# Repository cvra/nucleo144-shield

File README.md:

# CVRA Nucleo144 shield

## Requirements list
* Alim en entrée
 - 5V, bus + nucleo + shield (borne à visser)
 - 6V, servo (borne à visser)
* debug connector
* 2x CAN interface with CAN transceiver:
  - 6x Connector for one CAN interface (mounted as needed)
  - 3x Connector for other CAN interface (mounted as needed)
* Interface panel connector (20 pin)
  - 5V, GND (2 pin)
  - 2x CAN for debug (1 for each interface) (4 pin)
  - RGB LED (3 GPIO to control) (3 pin)
  - I/O (11 pin)
* 15x RC-Servo output: connecteur 3pin 2.54mm standard (+,-,signal). use PWM if available and GPIO for the rest (software PWM)
* 2x Encoder connector (5-pin Molex CHA, CHB, CHN, 5V, GND)
(3x Encoder connector if I/O available on MCU)
* Additional connectors (if I/O available on MCU)
  - 1x I2C Molex
  - 1x UART Molex
  - 1x SPI Molex
  - 4x GPIO (with 4x GND) on 2.54mm standard pin holes (no connector)
  - 1x 5V power to power board and distribute over CAN
* SDCard/SPI-flash for logging
* Mechanical dimension
  - Width and length, max same as Nucleo-144 board (70mmx108mm)
  - Maximum mechanical available space including output cable for Nucleo board and shield ( height = 36mm, lenght = 136.5mm)

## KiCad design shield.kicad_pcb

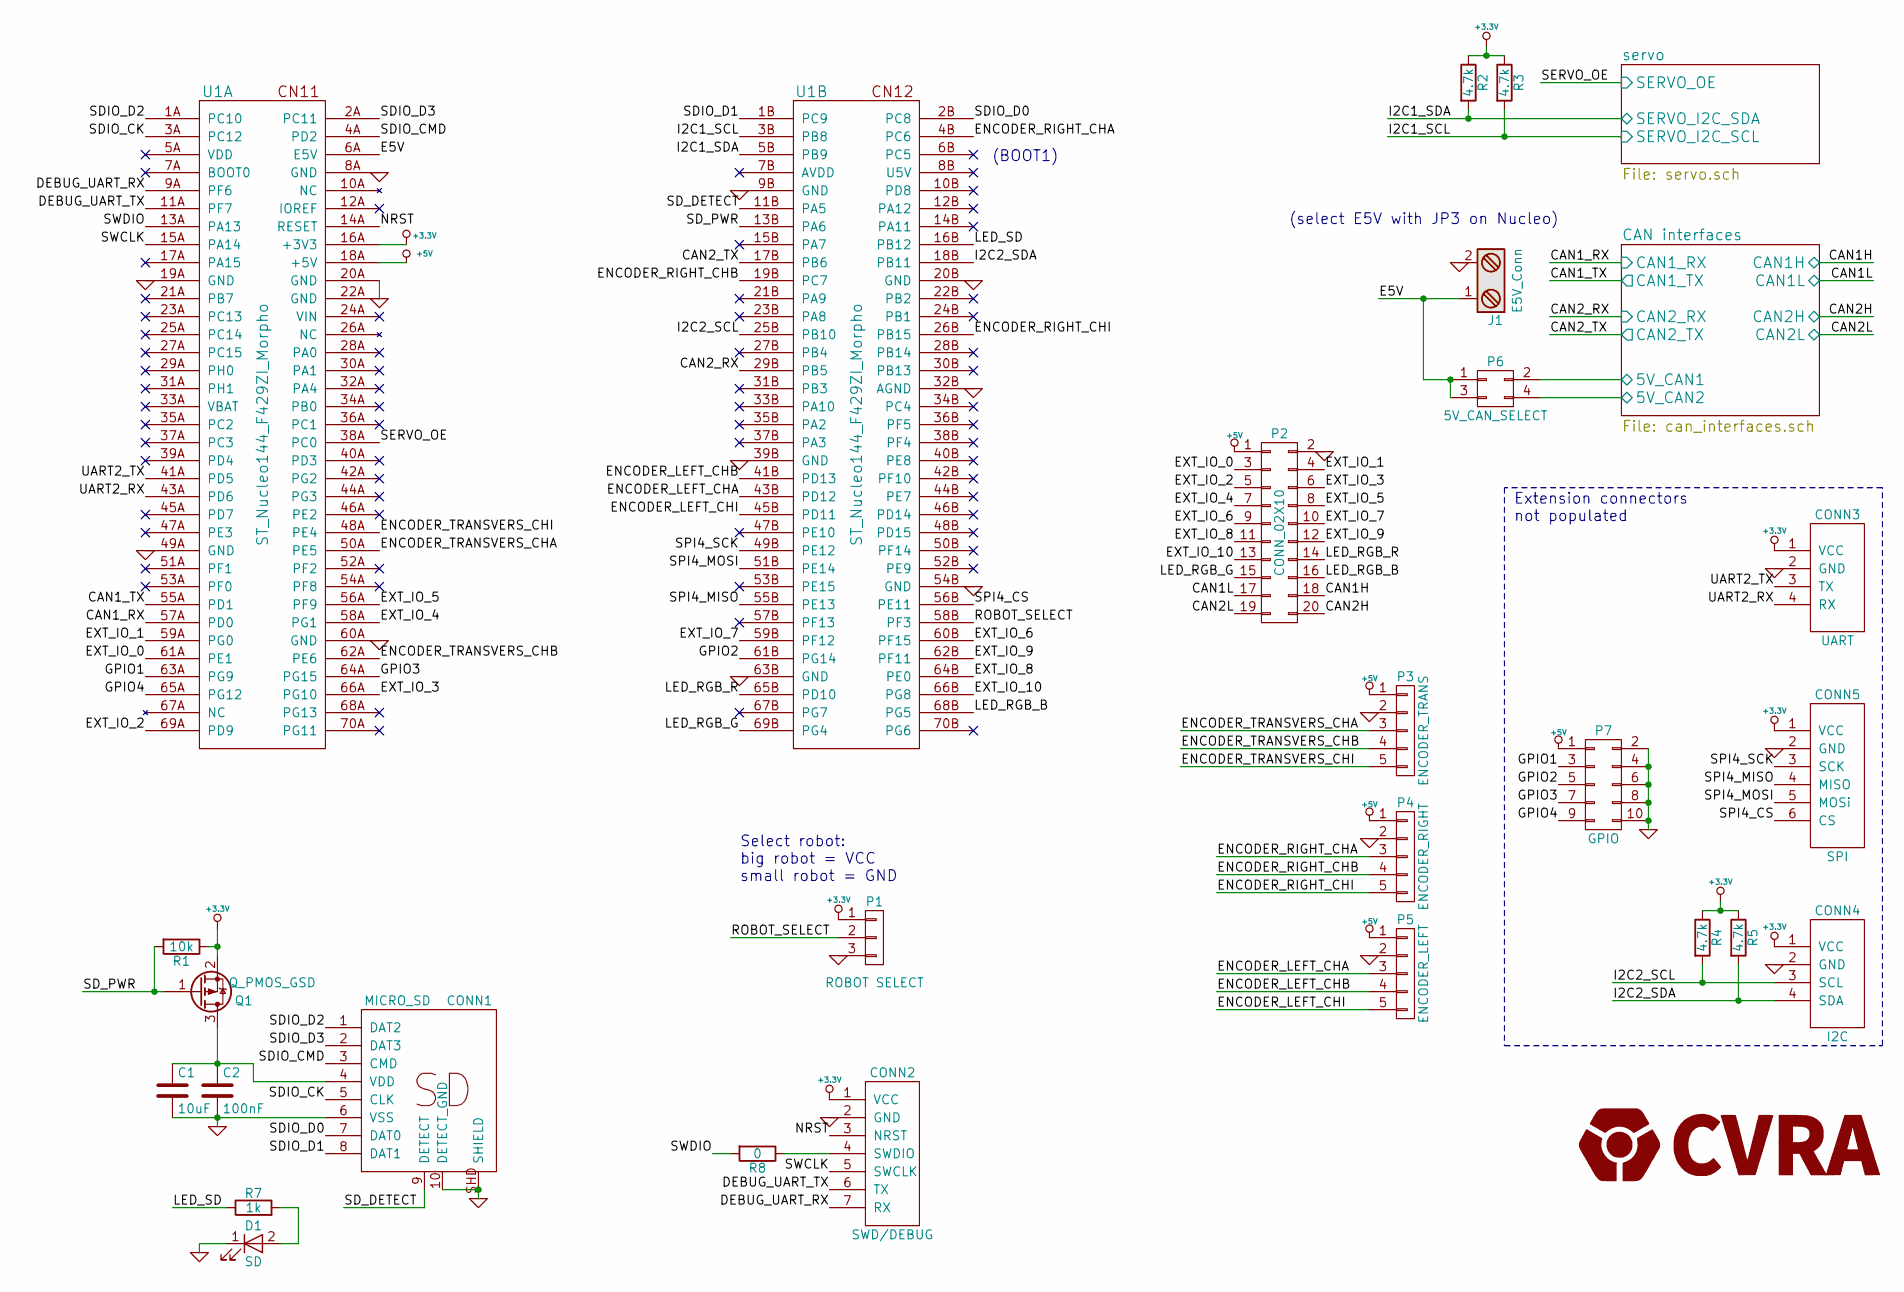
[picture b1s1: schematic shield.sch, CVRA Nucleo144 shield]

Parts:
C1: 10uF; C_0805
C2: 100nF; C_0805
CONN1: MICRO_SD; _Molex-microSD-502570-0893
CONN2: SWD/DEBUG; Molex_PicoBlade_53261-0771_07x1.25mm_Angled
CONN3: UART; Molex-PicoBlade-4
CONN4: I2C; Molex-PicoBlade-4
CONN5: SPI; Molex-PicoBlade-6
D1: SD; LED_0805
J1: E5V_Conn; TerminalBlock_Pheonix_MKDS1.5-2pol
P1: ROBOT SELECT; Pin_Header_Straight_1x03
P2: CONN_02X10; IDC_Header_Straight_20pins
P3: ENCODER_TRANS; Molex-PicoBlade-5
P4: ENCODER_RIGHT; Molex-PicoBlade-5
P5: ENCODER_LEFT; Molex-PicoBlade-5
P6: 5V_CAN_SELECT; Pin_Header_Straight_2x02
P7: GPIO; Pin_Header_Straight_2x05
Q1: Q_PMOS_GSD; SOT-23_Handsoldering
R1: 10k; R_0805
R2, R3, R4, R5: 4.7k; R_0805
R7: 1k; R_0805
R8: 0; R_0805
U1: ST_Nucleo144_F429ZI_Morpho

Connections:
+3.3V: CONN2.1 (VCC), CONN3.1 (VCC), CONN4.1 (VCC), CONN5.1 (VCC), P1.1, Q1.2 (S), R1.1, R2.1, R3.1, R4.1, R5.1, U1.16A (+3V3); also elsewhere on the board
+5V: P2.1, P3.1, P4.1, P5.1, P7.1, U1.18A (+5V); also elsewhere on the board
/CAN1H: P2.18; also elsewhere on the board
/CAN1L: P2.17; also elsewhere on the board
/CAN1_RX: U1.57A (PD0); also elsewhere on the board
/CAN1_TX: U1.55A (PD1); also elsewhere on the board
/CAN2H: P2.20; also elsewhere on the board
/CAN2L: P2.19; also elsewhere on the board
/CAN2_RX: U1.29B (PB5); also elsewhere on the board
/CAN2_TX: U1.17B (PB6); also elsewhere on the board
/CAN interfaces/5V_CAN1: P6.2; also elsewhere on the board
/CAN interfaces/5V_CAN2: P6.4; also elsewhere on the board
/DEBUG_UART_RX: CONN2.7 (RX), U1.9A (PF6)
/DEBUG_UART_TX: CONN2.6 (TX), U1.11A (PF7)
/E5V: J1.1, P6.1, P6.3, U1.6A (E5V)
/ENCODER_LEFT_CHA: P5.3, U1.43B (PD12)
/ENCODER_LEFT_CHB: P5.4, U1.41B (PD13)
/ENCODER_LEFT_CHI: P5.5, U1.45B (PD11)
/ENCODER_RIGHT_CHA: P4.3, U1.4B (PC6)
/ENCODER_RIGHT_CHB: P4.4, U1.19B (PC7)
/ENCODER_RIGHT_CHI: P4.5, U1.26B (PB15)
/ENCODER_TRANSVERS_CHA: P3.3, U1.50A (PE5)
/ENCODER_TRANSVERS_CHB: P3.4, U1.62A (PE6)
/ENCODER_TRANSVERS_CHI: P3.5, U1.48A (PE4)
/EXT_IO_0: P2.3, U1.61A (PE1)
/EXT_IO_1: P2.4, U1.59A (PG0)
/EXT_IO_2: P2.5, U1.69A (PD9)
/EXT_IO_3: P2.6, U1.66A (PG10)
/EXT_IO_4: P2.7, U1.58A (PG1)
/EXT_IO_5: P2.8, U1.56A (PF9)
/EXT_IO_6: P2.9, U1.60B (PF15)
/EXT_IO_7: P2.10, U1.59B (PF12)
/EXT_IO_8: P2.11, U1.64B (PE0)
/EXT_IO_9: P2.12, U1.62B (PF11)
/EXT_IO_10: P2.13, U1.66B (PG8)
/GPIO1: P7.3, U1.63A (PG9)
/GPIO2: P7.5, U1.61B (PG14)
/GPIO3: P7.7, U1.64A (PG15)
/GPIO4: P7.9, U1.65A (PG12)
/I2C1_SCL: R3.2, U1.3B (PB8); also elsewhere on the board
/I2C1_SDA: R2.2, U1.5B (PB9); also elsewhere on the board
/I2C2_SCL: CONN4.3 (SCL), R4.2, U1.25B (PB10)
/I2C2_SDA: CONN4.4 (SDA), R5.2, U1.18B (PB11)
/LED_RGB_B: P2.16, U1.68B (PG5)
/LED_RGB_G: P2.15, U1.69B (PG4)
/LED_RGB_R: P2.14, U1.65B (PD10)
/LED_SD: R7.1, U1.16B (PB12)
/NRST: CONN2.3 (NRST), U1.14A (RESET)
/ROBOT_SELECT: P1.2, U1.58B (PF3)
/SDIO_CK: CONN1.5 (CLK), U1.3A (PC12)
/SDIO_CMD: CONN1.3 (CMD), U1.4A (PD2)
/SDIO_D0: CONN1.7 (DAT0), U1.2B (PC8)
/SDIO_D1: CONN1.8 (DAT1), U1.1B (PC9)
/SDIO_D2: CONN1.1 (DAT2), U1.1A (PC10)
/SDIO_D3: CONN1.2 (DAT3), U1.2A (PC11)
/SD_DETECT: CONN1.9 (DETECT), U1.11B (PA5)
/SD_PWR: Q1.1 (G), R1.2, U1.13B (PA6)
/SERVO_OE: U1.38A (PC0); also elsewhere on the board
/SPI4_CS: CONN5.6 (CS), U1.56B (PE11)
/SPI4_MISO: CONN5.4 (MISO), U1.55B (PE13)
/SPI4_MOSI: CONN5.5 (MOSi), U1.51B (PE14)
/SPI4_SCK: CONN5.3 (SCK), U1.49B (PE12)
/SWCLK: CONN2.5 (SWCLK), U1.15A (PA14)
/SWDIO: R8.2, U1.13A (PA13)
/UART2_RX: CONN3.4 (RX), U1.43A (PD6)
/UART2_TX: CONN3.3 (TX), U1.41A (PD5)
GND: C1.2, C2.2, CONN1.6 (VSS), CONN1.10 (DETECT_GND), CONN1.SHD (SHIELD), CONN2.2 (GND), CONN3.2 (GND), CONN4.2 (GND), CONN5.2 (GND), D1.1 (K), J1.2, P1.3, P2.2, P3.2, P4.2, P5.2, P7.2, P7.4, P7.6, P7.8, P7.10, U1.8A (GND), U1.9B (GND), U1.19A (GND), U1.20A (GND), U1.20B (GND), U1.22A (GND), U1.32B (AGND), U1.39B (GND), U1.49A (GND), U1.54B (GND), U1.60A (GND), U1.63B (GND); also elsewhere on the board
unnamed: C1.1, C2.1, CONN1.4 (VDD), Q1.3 (D)
unnamed: CONN2.4 (SWDIO), R8.1
unnamed: D1.2 (A), R7.2

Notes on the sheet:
Select robot: big robot = VCC small robot = GND
(BOOT1)
(select E5V with JP3 on Nucleo)
Extension connectors not populated

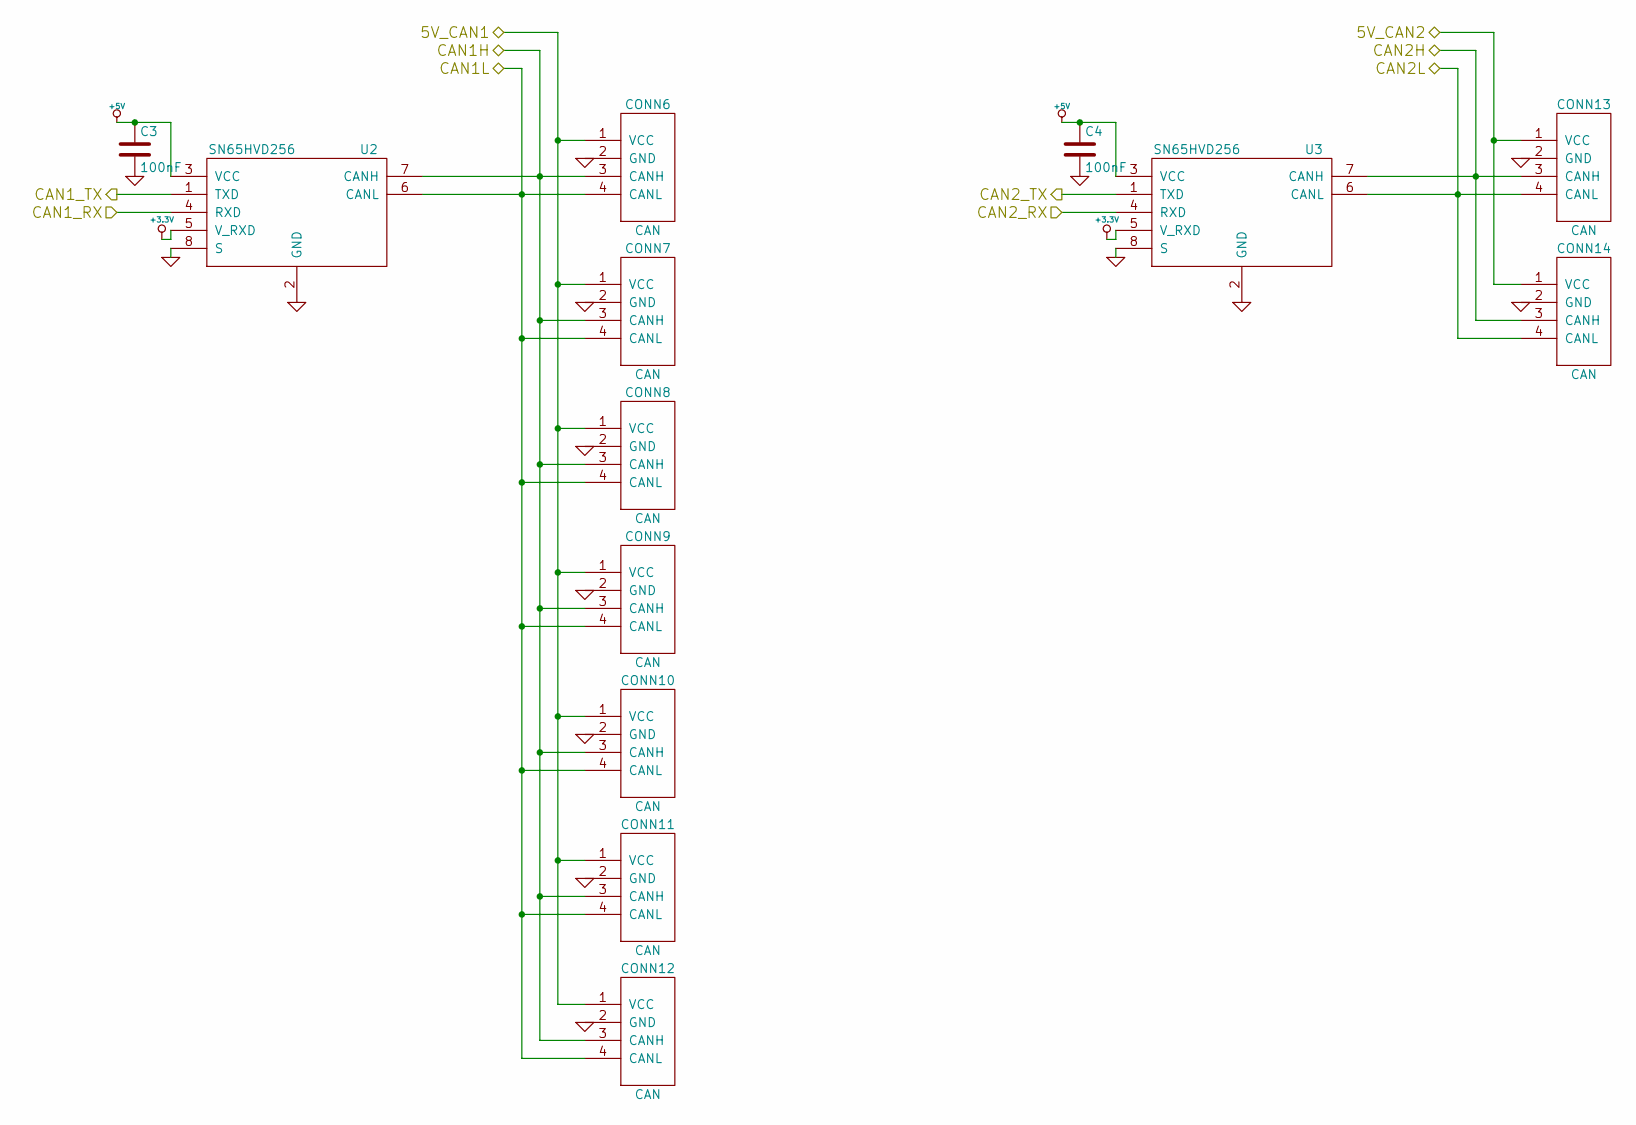
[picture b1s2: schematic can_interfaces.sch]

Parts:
C3, C4: 100nF; C_0805
CONN6, CONN7, CONN8, CONN9, CONN10, CONN11, CONN12, CONN13, CONN14: CAN; _Molex-PicoBlade-SMD-4
U2, U3: SN65HVD256; SOIC-8_3.9x4.9mm_Pitch1.27mm

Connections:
+3.3V: U2.5 (V_RXD), U3.5 (V_RXD); also elsewhere on the board
+5V: C3.1, C4.1, U2.3 (VCC), U3.3 (VCC); also elsewhere on the board
/CAN1H: CONN6.3 (CANH), CONN7.3 (CANH), CONN8.3 (CANH), CONN9.3 (CANH), CONN10.3 (CANH), CONN11.3 (CANH), CONN12.3 (CANH), U2.7 (CANH); also elsewhere on the board
/CAN1L: CONN6.4 (CANL), CONN7.4 (CANL), CONN8.4 (CANL), CONN9.4 (CANL), CONN10.4 (CANL), CONN11.4 (CANL), CONN12.4 (CANL), U2.6 (CANL); also elsewhere on the board
/CAN1_RX: U2.4 (RXD); also elsewhere on the board
/CAN1_TX: U2.1 (TXD); also elsewhere on the board
/CAN2H: CONN13.3 (CANH), CONN14.3 (CANH), U3.7 (CANH); also elsewhere on the board
/CAN2L: CONN13.4 (CANL), CONN14.4 (CANL), U3.6 (CANL); also elsewhere on the board
/CAN2_RX: U3.4 (RXD); also elsewhere on the board
/CAN2_TX: U3.1 (TXD); also elsewhere on the board
/CAN interfaces/5V_CAN1: CONN6.1 (VCC), CONN7.1 (VCC), CONN8.1 (VCC), CONN9.1 (VCC), CONN10.1 (VCC), CONN11.1 (VCC), CONN12.1 (VCC); also elsewhere on the board
/CAN interfaces/5V_CAN2: CONN13.1 (VCC), CONN14.1 (VCC); also elsewhere on the board
GND: C3.2, C4.2, CONN6.2 (GND), CONN6.MECH (GND), CONN7.2 (GND), CONN7.MECH (GND), CONN8.2 (GND), CONN8.MECH (GND), CONN9.2 (GND), CONN9.MECH (GND), CONN10.2 (GND), CONN10.MECH (GND), CONN11.2 (GND), CONN11.MECH (GND), CONN12.2 (GND), CONN12.MECH (GND), CONN13.2 (GND), CONN13.MECH (GND), CONN14.2 (GND), CONN14.MECH (GND), U2.2 (GND), U2.8 (S), U3.2 (GND), U3.8 (S); also elsewhere on the board

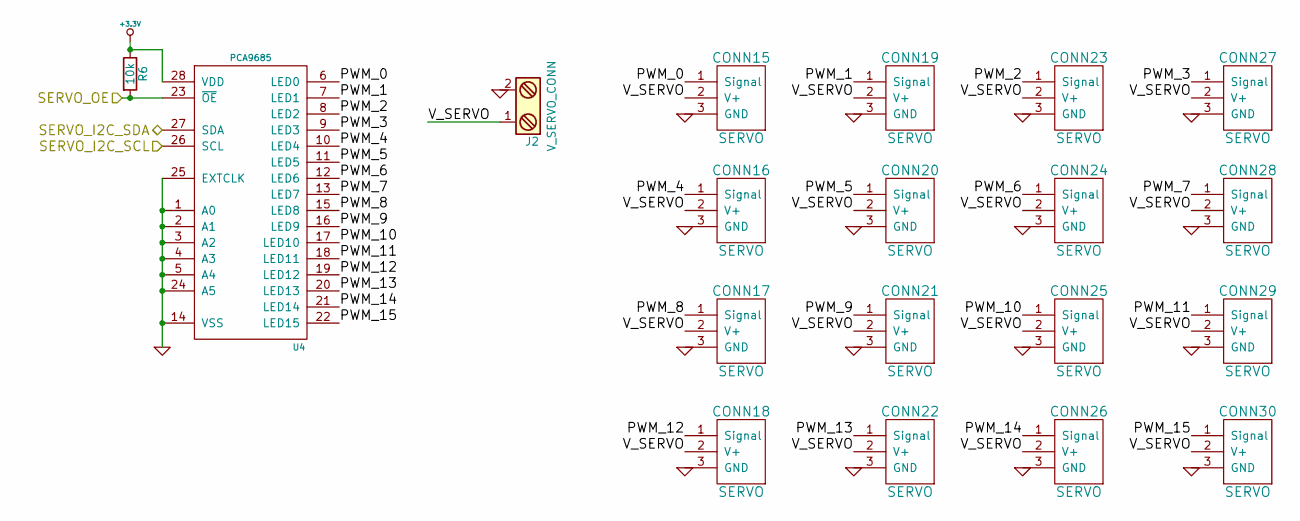
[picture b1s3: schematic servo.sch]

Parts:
CONN15, CONN16, CONN17, CONN18, CONN19, CONN20, CONN21, CONN22, CONN23, CONN24, CONN25, CONN26, CONN27, CONN28, CONN29, CONN30: SERVO; Pin_Header_Straight_1x03
J2: V_SERVO_CONN; TerminalBlock_Pheonix_MKDS1.5-2pol
R6: 10k; R_0805
U4: PCA9685; TSSOP-28_4.4x9.7mm_Pitch0.65mm

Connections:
+3.3V: R6.1, U4.28 (VDD); also elsewhere on the board
/I2C1_SCL: U4.26 (SCL); also elsewhere on the board
/I2C1_SDA: U4.27 (SDA); also elsewhere on the board
/SERVO_OE: R6.2, U4.23 (~OE); also elsewhere on the board
/servo/PWM_0: CONN15.1 (Signal), U4.6 (LED0)
/servo/PWM_1: CONN19.1 (Signal), U4.7 (LED1)
/servo/PWM_2: CONN23.1 (Signal), U4.8 (LED2)
/servo/PWM_3: CONN27.1 (Signal), U4.9 (LED3)
/servo/PWM_4: CONN16.1 (Signal), U4.10 (LED4)
/servo/PWM_5: CONN20.1 (Signal), U4.11 (LED5)
/servo/PWM_6: CONN24.1 (Signal), U4.12 (LED6)
/servo/PWM_7: CONN28.1 (Signal), U4.13 (LED7)
/servo/PWM_8: CONN17.1 (Signal), U4.15 (LED8)
/servo/PWM_9: CONN21.1 (Signal), U4.16 (LED9)
/servo/PWM_10: CONN25.1 (Signal), U4.17 (LED10)
/servo/PWM_11: CONN29.1 (Signal), U4.18 (LED11)
/servo/PWM_12: CONN18.1 (Signal), U4.19 (LED12)
/servo/PWM_13: CONN22.1 (Signal), U4.20 (LED13)
/servo/PWM_14: CONN26.1 (Signal), U4.21 (LED14)
/servo/PWM_15: CONN30.1 (Signal), U4.22 (LED15)
/servo/V_SERVO: CONN15.2 (V+), CONN16.2 (V+), CONN17.2 (V+), CONN18.2 (V+), CONN19.2 (V+), CONN20.2 (V+), CONN21.2 (V+), CONN22.2 (V+), CONN23.2 (V+), CONN24.2 (V+), CONN25.2 (V+), CONN26.2 (V+), CONN27.2 (V+), CONN28.2 (V+), CONN29.2 (V+), CONN30.2 (V+), J2.1
GND: CONN15.3 (GND), CONN16.3 (GND), CONN17.3 (GND), CONN18.3 (GND), CONN19.3 (GND), CONN20.3 (GND), CONN21.3 (GND), CONN22.3 (GND), CONN23.3 (GND), CONN24.3 (GND), CONN25.3 (GND), CONN26.3 (GND), CONN27.3 (GND), CONN28.3 (GND), CONN29.3 (GND), CONN30.3 (GND), J2.2, U4.1 (A0), U4.2 (A1), U4.3 (A2), U4.4 (A3), U4.5 (A4), U4.14 (VSS), U4.24 (A5), U4.25 (EXTCLK); also elsewhere on the board

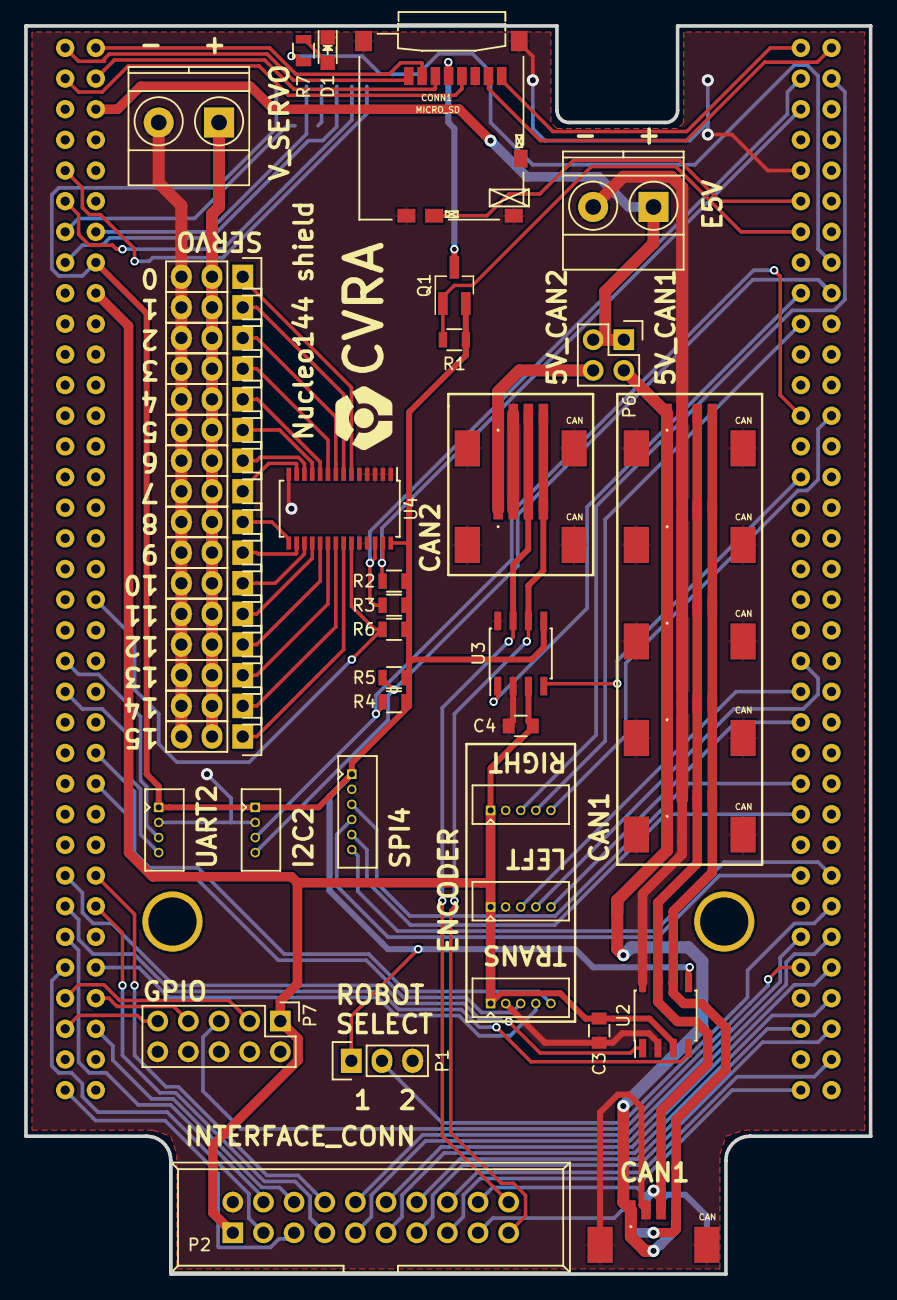
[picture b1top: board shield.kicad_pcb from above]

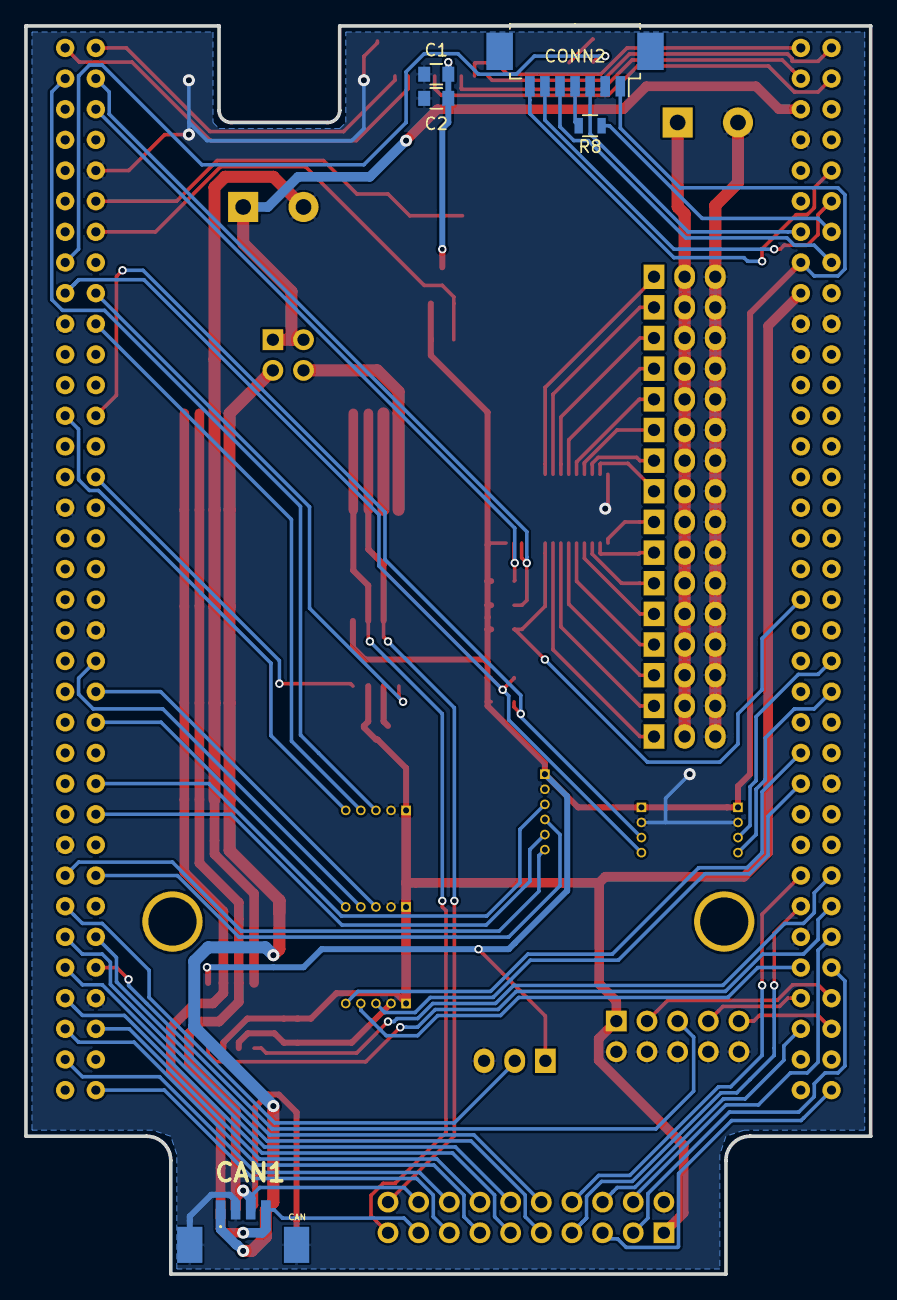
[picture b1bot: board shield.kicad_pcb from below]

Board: 2 copper layers, 70.0 x 103.4 mm, 59 parts (5 on the bottom side), 87 nets.

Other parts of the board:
_M2, _M2#2: VAL**; _M2

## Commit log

2016-09-19 start with schematic
2016-10-30 pinout doc
2016-10-31 add CAN interfaces with connectors
2016-11-06 SD card
2016-11-21 interface panel connector
2016-12-21 gpio assignment, servos PWM chip
2017-01-04 pin assignment, separate CAN_5V
2017-02-22 pin assignment, symbol placement
2017-03-04 footprint assignment
2017-03-04 place parts in PCB
2017-03-06 PCB routing
2017-03-06 change some GPIOs, finish routing
2017-03-06 fix SD PMOS switch pinout
2017-03-06 schema pdf
2017-03-06 README with image
2017-03-06 add datasheets
2017-03-06 gerber files
